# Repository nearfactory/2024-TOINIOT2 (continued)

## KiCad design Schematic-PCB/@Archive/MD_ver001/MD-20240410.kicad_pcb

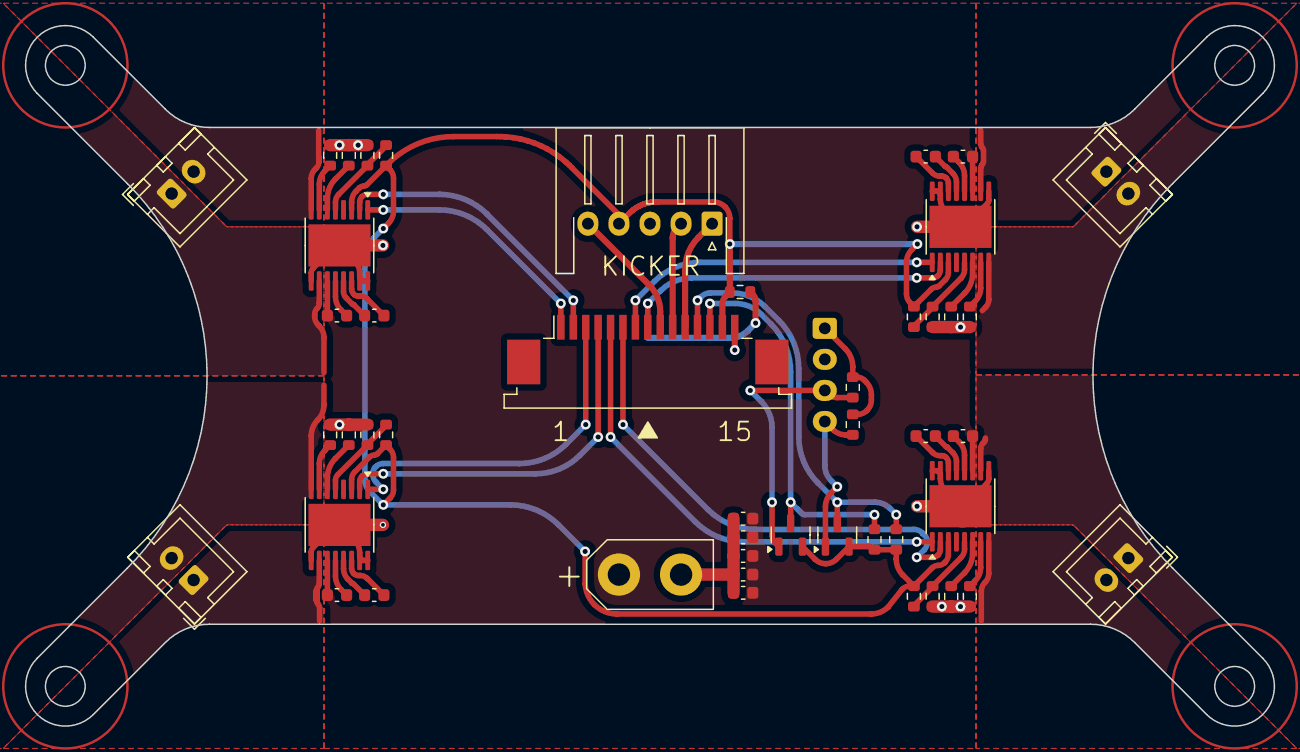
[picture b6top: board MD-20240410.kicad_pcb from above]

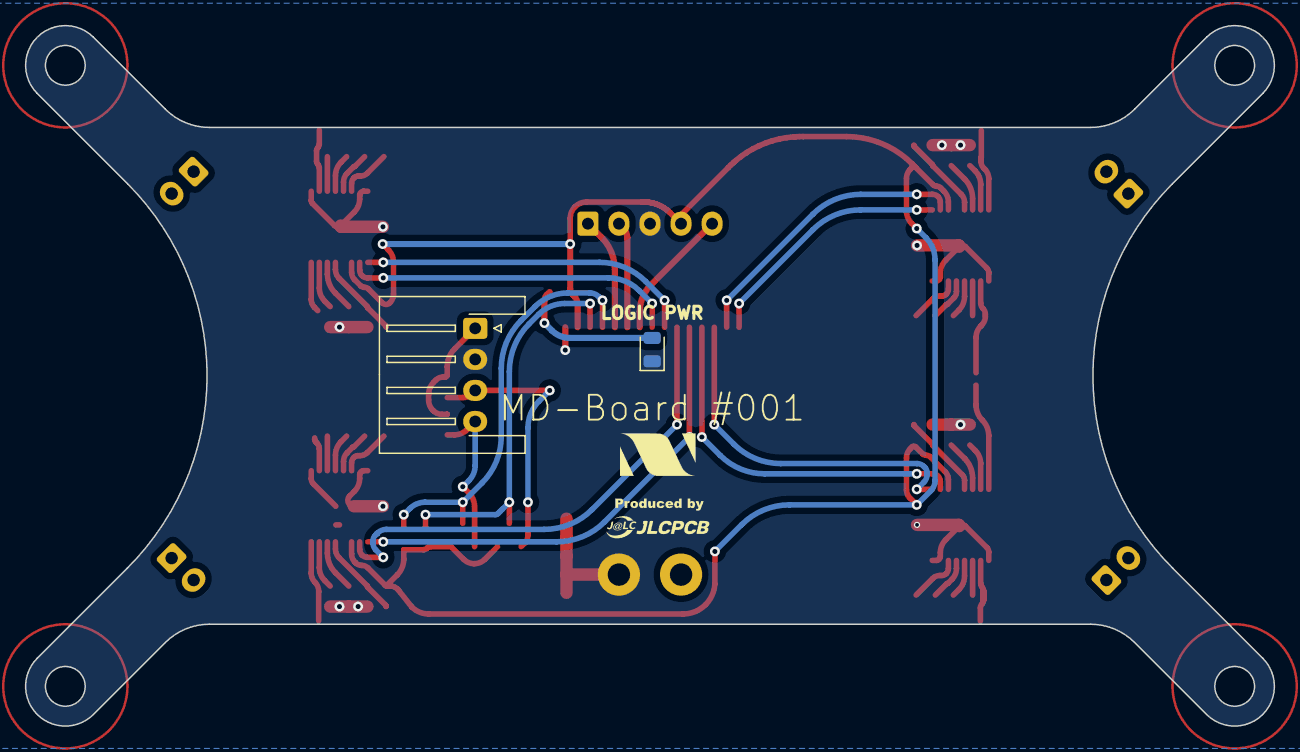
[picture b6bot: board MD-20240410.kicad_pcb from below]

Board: 2 copper layers, 100.5 x 56.4 mm, 49 parts (2 on the bottom side), 52 nets.

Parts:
C1, C9, C11, C13: 22n; C_0603_1608Metric
C2, C10, C12, C14: 220n; C_0603_1608Metric
C3, C4: 4.7u; C_0603_1608Metric
C5: 50u; C_0603_1608Metric
C7, C8: 0.1u; C_0603_1608Metric
D1: LED; LED_0805_2012Metric
J1: Conn_01x05_Pin; JST_XH_S5B-XH-A-1_1x05_P2.50mm_Horizontal
J2: Conn_01x04_Pin; JST_XH_S4B-XH-A-1_1x04_P2.50mm_Horizontal
J3, J4, J5, J6: Conn_01x02_Pin; JST_XH_B2B-XH-A_1x02_P2.50mm_Vertical
J7: Conn_01x02_Pin; XT30U-M
J8: Conn_01x15_Pin; TE_1-84953-5_1x15-1MP_P1.0mm_Horizontal
Q3, Q4: NMOS; SOT-23
R1: 330; R_0603_1608Metric
R3, R9, R13, R17, R20, R21, R22, R23: 10k; R_0603_1608Metric
R4, R8, R12, R16: 2.49k; R_0603_1608Metric
R6, R10, R14, R18: NP; R_0603_1608Metric
R7, R11, R15, R19: 20k; R_0603_1608Metric
U1, U2, U3, U4: HTSSOP-16-1EP_4.4x5mm_P0.65mm_EP3.4x5mm_Mask2.46x2.31mm

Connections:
+5V: J2.1, R21.1, R23.1
EN-1: J8.1, U1.1 (EN)
EN-2: J8.3, U2.1 (EN)
EN-3: J8.5, U3.1 (EN)
EN-4: J8.7, U4.1 (EN)
GND: C3.2, C4.2, C5.2, C7.2, C8.2, D1.1 (K), J1.3, J2.2, J7.2, J8.15, R4.2, R6.2, R7.2, R8.2, R10.2, R11.2, R12.2, R14.2, R15.2, R16.2, R18.2, R19.2, U1.9 (PGND), U1.15 (GND), U1.16 (PMODE), U1.17 (GND), U2.9 (PGND), U2.15 (GND), U2.16 (PMODE), U2.17 (GND), U3.9 (PGND), U3.15 (GND), U3.16 (PMODE), U3.17 (GND), U4.9 (PGND), U4.15 (GND), U4.16 (PMODE), U4.17 (GND)
IMODE-1: R7.1, U1.7 (IMODE)
IMODE-2: R11.1, U2.7 (IMODE)
IMODE-3: R15.1, U3.7 (IMODE)
IMODE-4: R19.1, U4.7 (IMODE)
KickerSignal-main: J1.2, J8.10
Line-MD-Main=RX_3.3V: J8.12, Q3.3 (S), R20.1
Line-MD-Main=RX_5V: J2.4, Q3.1 (D), R21.2
Line-MD-Main=TX_3.3V: J8.13, Q4.3 (S), R22.1
Line-MD-Main=TX_5V: J2.3, Q4.1 (D), R23.2
unnamed: D1.2 (A), R1.2
unnamed: C1.2, U1.13 (CPH)
unnamed: C1.1, U1.14 (CPL)
unnamed: R4.1, U1.6 (IPROPI)
unnamed: C2.1, U1.12 (VCP)
unnamed: C9.2, U2.13 (CPH)
unnamed: C9.1, U2.14 (CPL)
unnamed: R8.1, U2.6 (IPROPI)
unnamed: C10.1, U2.12 (VCP)
unnamed: C11.2, U3.13 (CPH)
unnamed: C11.1, U3.14 (CPL)
unnamed: R12.1, U3.6 (IPROPI)
unnamed: C12.1, U3.12 (VCP)
unnamed: C13.2, U4.13 (CPH)
unnamed: C13.1, U4.14 (CPL)
unnamed: R16.1, U4.6 (IPROPI)
unnamed: C14.1, U4.12 (VCP)
OUT1-1: J3.2, U1.8 (OUT1)
OUT1-2: J4.2, U2.8 (OUT1)
OUT1-3: J5.2, U3.8 (OUT1)
OUT1-4: J6.2, U4.8 (OUT1)
OUT2-1: J3.1, U1.10 (OUT2)
OUT2-2: J4.1, U2.10 (OUT2)
OUT2-3: J5.1, U3.10 (OUT2)
OUT2-4: J6.1, U4.10 (OUT2)
PH-1: J8.2, U1.2 (PH)
PH-2: J8.4, U2.2 (PH)
PH-3: J8.6, U3.2 (PH)
PH-4: J8.8, U4.2 (PH)
SLEEP-1: J1.4, J8.14, Q3.2 (G), Q4.2 (G), R1.1, R3.1, R9.1, R13.1, R17.1, R20.2, R22.2, U1.3 (SLEEP), U2.3 (SLEEP), U3.3 (SLEEP), U4.3 (SLEEP)
VM: C2.2, C3.1, C4.1, C5.1, C7.1, C8.1, C10.2, C12.2, C14.2, J7.1, U1.11 (VM), U2.11 (VM), U3.11 (VM), U4.11 (VM)
VREF-1: R3.2, R6.1, U1.5 (VREF)
VREF-2: R9.2, R10.1, U2.5 (VREF)
VREF-3: R13.2, R14.1, U3.5 (VREF)
VREF-4: R17.2, R18.1, U4.5 (VREF)
ball01k: J1.5, J8.9
ball02k: J1.1, J8.11
